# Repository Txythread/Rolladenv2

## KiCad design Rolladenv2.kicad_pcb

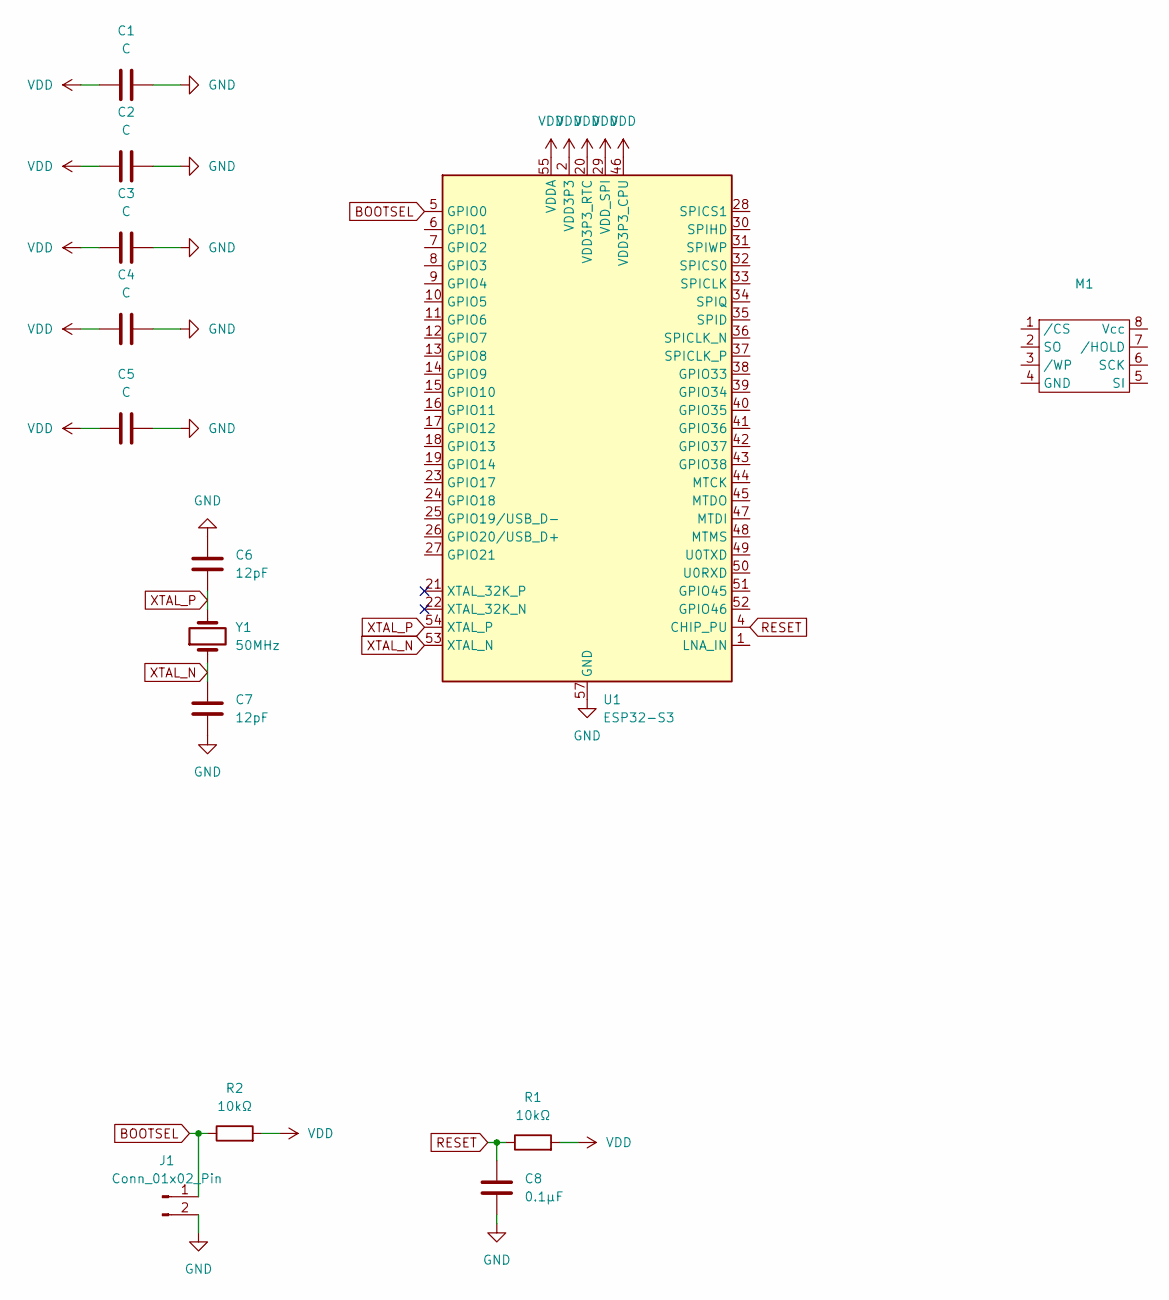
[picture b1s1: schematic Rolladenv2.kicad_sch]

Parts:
C1, C2, C3, C4, C5: C; C_0805_2012Metric_Pad1.18x1.45mm_HandSolder
C6, C7: 12pF; C_0603_1608Metric_Pad1.08x0.95mm_HandSolder
C8: 0.1µF; C_0805_2012Metric_Pad1.18x1.45mm_HandSolder
J1: Conn_01x02_Pin; PinHeader_1x02_P2.54mm_Vertical
M1: SON127P500X600X60-9N
R1, R2: 10kΩ; R_0805_2012Metric_Pad1.20x1.40mm_HandSolder
U1: ESP32-S3; QFN-56-1EP_7x7mm_P0.4mm_EP4x4mm
Y1: 50MHz; Crystal_SMD_MicroCrystal_CC4V-T1A-2Pin_5.0x1.9mm_HandSolder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

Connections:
BOOTSEL: J1.1, R2.1, U1.5 (GPIO0)
GND: C1.2, C2.2, C3.2, C4.2, C5.2, C6.1, C7.1, C8.2, J1.2, U1.57 (GND)
RESET: C8.1, R1.1, U1.4 (CHIP_PU)
VDD: C1.1, C2.1, C3.1, C4.1, C5.1, R1.2, R2.2, U1.2 (VDD3P3), U1.3 (VDD3P3), U1.20 (VDD3P3_RTC), U1.29 (VDD_SPI), U1.46 (VDD3P3_CPU), U1.55 (VDDA), U1.56 (VDDA)
XTAL_N: C7.2, U1.53 (XTAL_N), Y1.1
XTAL_P: C6.2, U1.54 (XTAL_P), Y1.2

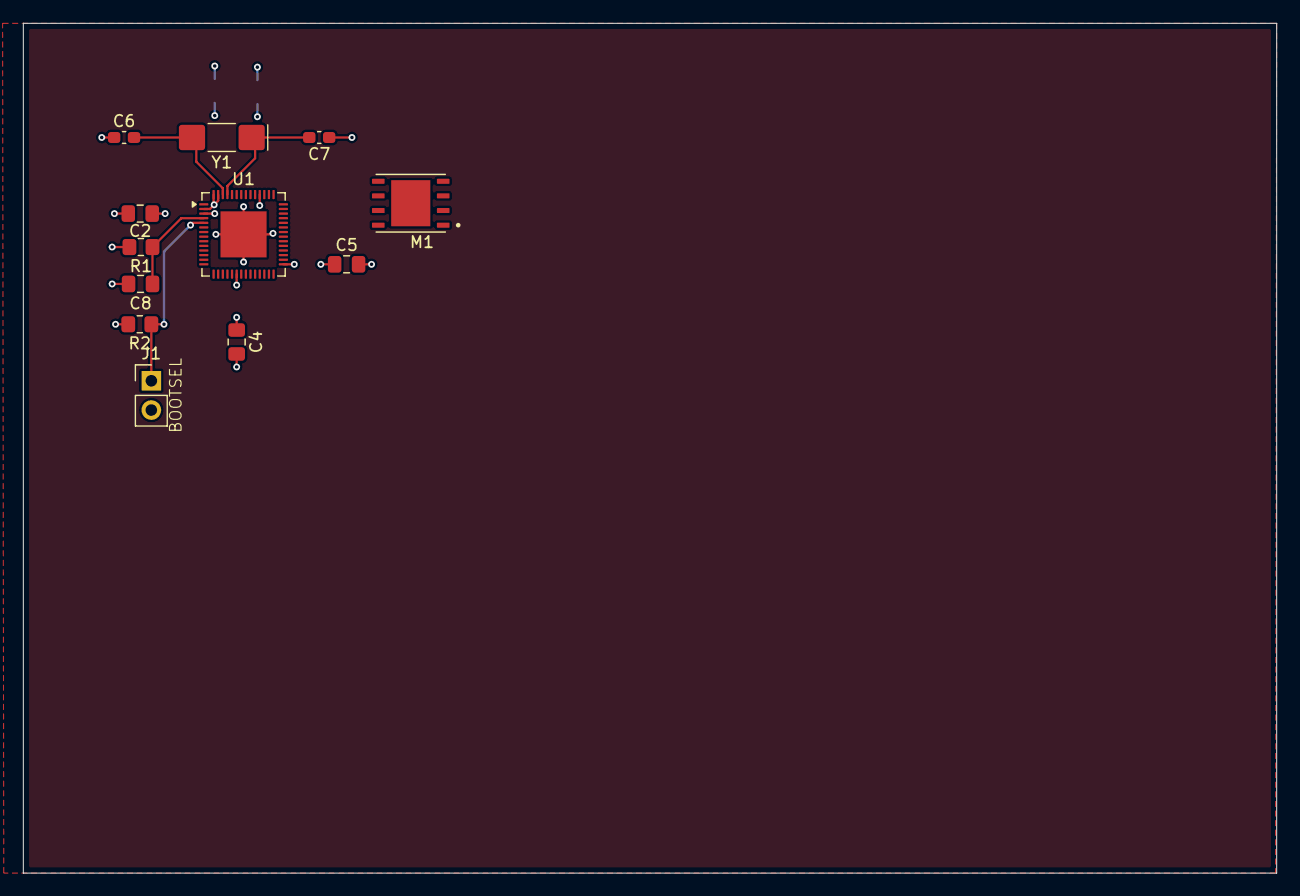
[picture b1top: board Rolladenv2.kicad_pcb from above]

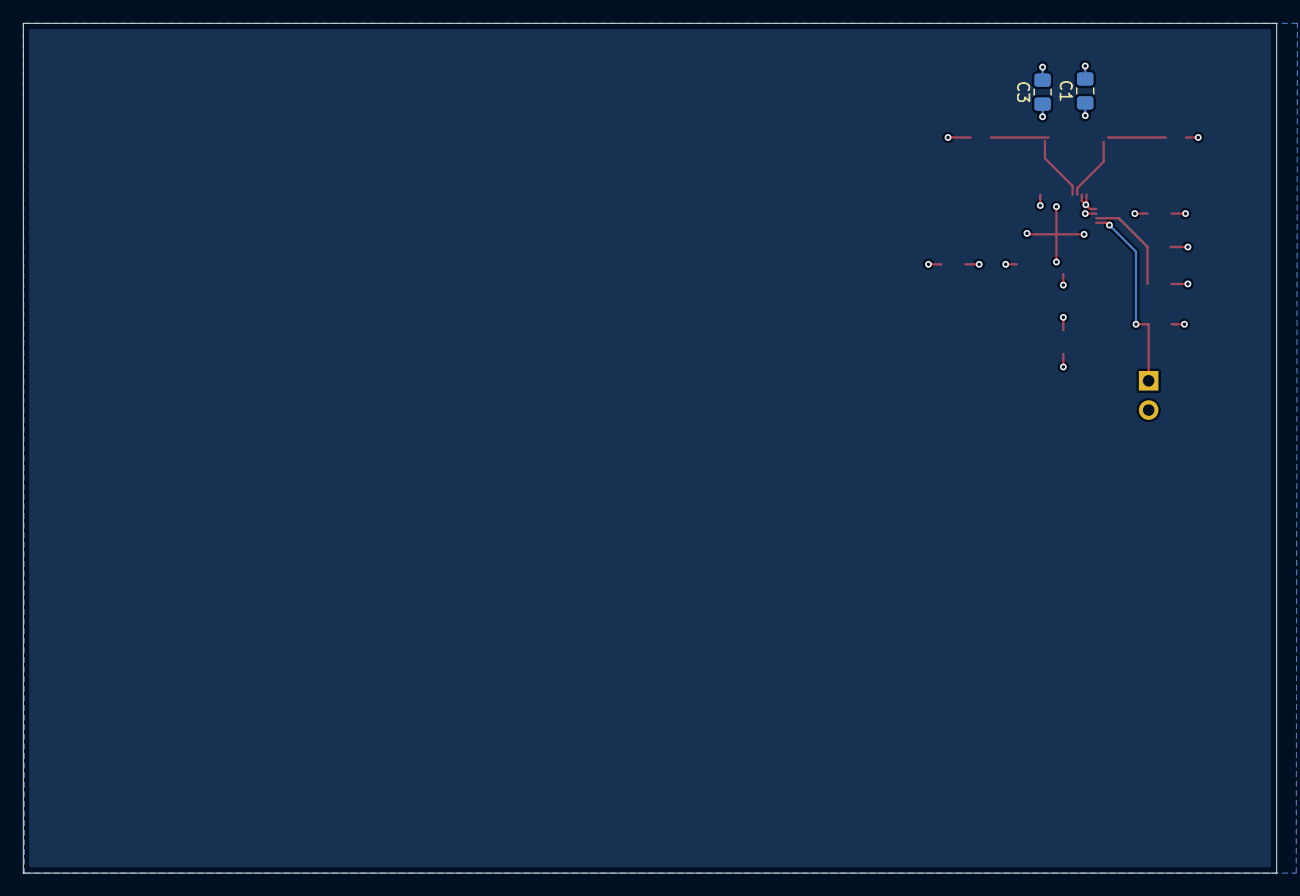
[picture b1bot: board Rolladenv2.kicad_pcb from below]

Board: 4 copper layers, 108.7 x 73.7 mm, 14 parts (2 on the bottom side), 6 nets.

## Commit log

2026-01-05 Create LICENSE
2026-01-05 Added Caps and XTAL
2026-01-05 Added Reset Circuitry
2026-01-05 Added Flash Data
